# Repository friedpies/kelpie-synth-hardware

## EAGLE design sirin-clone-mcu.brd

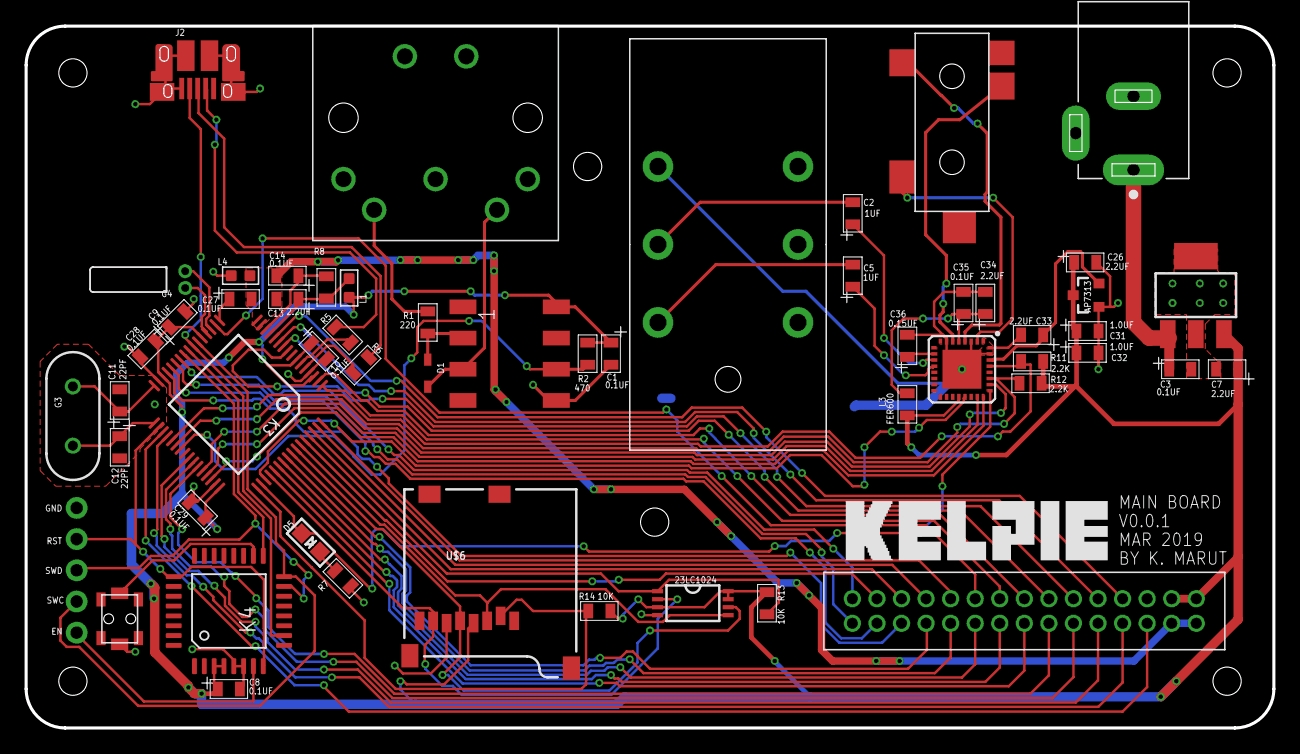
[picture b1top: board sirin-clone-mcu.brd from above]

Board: 2 copper layers, 101.6 x 57.1 mm, 55 parts (0 on the bottom side), 74 nets.

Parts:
C1, C3, C8, C9, C10, C14, C27, C28, C29, C35: 0.1UF; C_0805
C2, C5: 1UF; C_0805
C7, C13, C26, C33, C34: 2.2UF; C_0805
C11, C12: 22PF; C_0805
C31, C32: 1.0UF; C_0805
C36: 0.15UF; C_0805
D1: 1N4148WX-TP; SOD323
D5: ORANGE; CHIPLED_0805
D6: AP7313; SOT23-3
G3: 16MHz; HC49US
G4: 32.768kHz; TC26H
J1: PJ-002A; CUI_PJ-002A
J2: USB-MICROB-PTH-MILL
J3: 30_PIN_CONNECTOR_MALE; MOLEX_30PINCONNECTOR_2MM
J5: SWITCHCRAFT_PHONEJACK; STEREO_JACK_2SWITCH
J6: SWD_CONNECTOR; 1X5HEADER
K3: LQFP64-05
K4: LQFP32-08
L1, L4: L0603
L3: FER600; 0805
OK1: 6N138; DIP8
R1: 220; 0805
R2, R7, R8: 470; 0805
R5, R6: 33; 0805
R11, R12: 2.2K; 0805
R13, R14: 10K; 0805
S2: SWITCH_PTS820
T2: MCP1825S; SOT-223
U4: SGTL5000_32QFN; QFN-32-5MM
U5: 23LC1024; TSSOP8
U$1: MIDI_CONNECTOR; DIN_SDS_50J
U$3: STEREO_LINE_OUT_JACK; AMPHENOL_STEREO_JACK
U$6: MICROSD; MICRO-SD-SOCKET

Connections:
3.3V: C1.+, C7.+, C8.+, C9.+, C10.+, C26.+, C28.+, C29.+, C31.+, C32.+, D6.IN, J3.P$14, J3.P$15, K3.3, K3.7, K3.21, K3.30, K3.48, K4.3, K4.4, L1.2, L3.1, OK1.8, R2.2, R11.2, R12.2, R13.1, R14.2, T2.3, U4.20, U5.3, U5.7, U5.8, U$6.VCC(4)
AGND: C13.-, C14.-, C27.-, J3.P$29, J3.P$30, K3.15, K3.16, L4.2
AREF: C14.+, K3.14, R8.2
D+: J2.D+, R6.1
D-: J2.D-, R5.1
EN': J6.5, K4.7
GND: C1.-, C3.-, C7.-, C8.-, C9.-, C10.-, C11.-, C12.-, C26.-, C28.-, C29.-, C31.-, C32.-, C33.-, C34.-, C35.-, C36.-, D6.GND, J1.2, J2.GND, J2.SHIELD, J2.SHIELD2, J2.SHIELD3, J2.SHIELD4, J2.SHIELD5, J2.SHIELD6, J2.SHIELD7, J2.SHIELD8, J2.SHIELD9, J2.SHIELD10, J3.P$13, J6.1, K3.4, K3.31, K3.47, K4.5, K4.6, L4.1, OK1.5, R7.1, S2.2, T2.2, T2.PAD, U4.1, U4.3, U4.7, U4.31, U4.32, U4.PAD, U5.4, U$3.4, U$6.GND(6)
unnamed: D1.A, OK1.3, U$1.5
unnamed: R1.2, U$1.4
unnamed: D1.C, OK1.2, R1.1
unnamed: C5.+, U4.12
unnamed: C2.+, U4.11
unnamed: C2.-, U$3.5
unnamed: K3.24, K4.17
unnamed: D5.C, R7.2
unnamed: G4.1, K3.20
unnamed: G4.2, K3.19
unnamed: C12.+, G3.2, K3.33
unnamed: C11.+, G3.1, K3.32
unnamed: C13.+, K3.13, L1.1, R8.1
unnamed: C27.+, K3.17
unnamed: C5.-, U$3.6
unnamed: C36.+, U4.10
unnamed: C33.+, D6.OUT, U4.30
unnamed: C34.+, C35.+, L3.2, U4.5
PIN0/MIDIIN: K3.39, OK1.6, R2.1
PIN2/SW1: J3.P$19, K3.57
PIN3/SW2: J3.P$17, K3.28
PIN4/SW3: J3.P$18, K3.29
PIN5/SW4: J3.P$5, K3.64
PIN6/CS: K3.61, R13.2, U5.1
PIN7/CMD: K3.59, U5.5, U$6.DI(3)
PIN8/MIDILED: J3.P$2, K3.60
PIN9/BCLK: K3.46, U4.24
PIN10/DAT3: K3.49, R14.1, U$6.CS(2)
PIN11/MCLK: K3.51, U4.21
PIN12/DAT0: K3.52, U5.2, U$6.DO(7)
PIN13/RX: D5.A, K3.50, U4.25
PIN14/CLK: K3.58, U5.6, U$6.SCLK(5)
PIN15/KNOB1(VOL): J3.P$24, K3.43
PIN16/KNOB2: J3.P$28, K3.35
PIN17/KNOB3: J3.P$27, K3.36
PIN18/SDA: K3.38, R12.1, U4.27
PIN19/SCL: K3.37, R11.1, U4.29
PIN20/KNOB4: J3.P$3, K3.62
PIN21/KNOB5: J3.P$4, K3.63
PIN22/TX: K3.44, U4.26
PIN23/LRCLK: K3.45, U4.23
PIN24/LED1: J3.P$16, K3.27
PIN25/LED2: J3.P$25, K3.42
PIN26/KNOB6: J3.P$8, K3.2
PIN27/KNOB7: J3.P$22, K3.54
PIN28/KNOB8: J3.P$23, K3.53
PIN29/KNOB9: J3.P$21, K3.55
PIN30/KNOB10: J3.P$20, K3.56
PIN31/KNOB11: J3.P$7, K3.1
PIN32/LED3: J3.P$26, K3.41
PIN33/LED4: J3.P$1, K3.26
PINA10/KNOB12: J3.P$10, K3.9
PINA11/KNOB13: J3.P$9, K3.10
PINA12/KNOB14: J3.P$11, K3.11
PINA13/KNOB15: J3.P$12, K3.12
PINA14/KNOB16: J3.P$6, K3.18
PROG: K4.18, S2.1
RING/R: J5.3, U4.2
RST: J6.2, K3.34, K4.8, K4.25
SLEEVE: J5.1, U4.4
SWC: J6.4, K3.22, K4.16
SWD: J6.3, K3.25, K4.15
TIP/L: J5.2, U4.6
USB_DM: K3.6, R5.2
USB_DP: K3.5, R6.2
USB_ID: J2.ID, K3.23, K4.10
VIN_5V: C3.+, J1.1, T2.1

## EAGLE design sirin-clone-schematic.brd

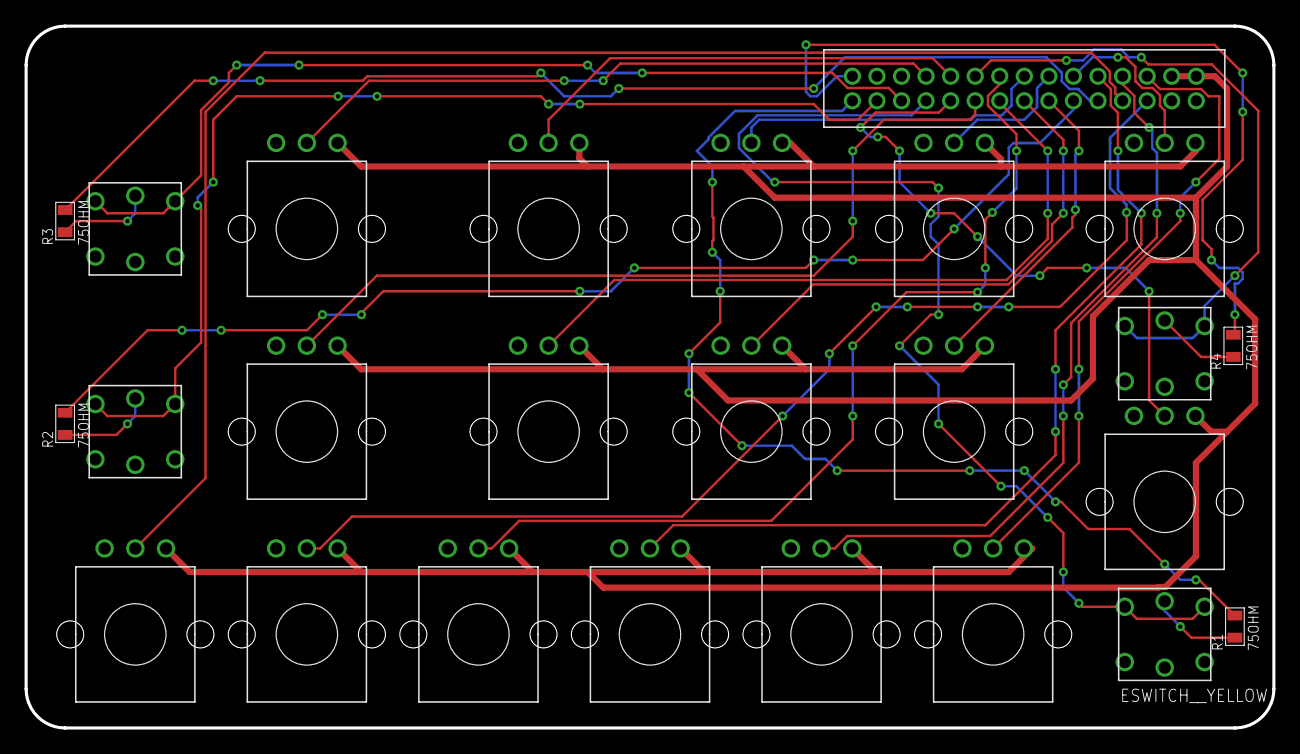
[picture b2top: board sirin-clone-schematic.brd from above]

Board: 2 copper layers, 101.6 x 57.1 mm, 25 parts (0 on the bottom side), 30 nets.

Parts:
J1: 30_PIN_CONNECTOR_MALE; MOLEX_30PINCONNECTOR_2MM
R1, R2, R3, R4: 75OHM; 0805
U$1, U$2, U$3, U$4, U$5, U$6, U$7, U$8, U$9, U$10, U$12, U$13, U$14, U$15, U$16, U$17: BOURNS_20K_POTENTIOMETER; BOURNS_PTV09
U$18, U$19, U$20, U$21: ESWITCH__YELLOW; ESWITCH_TL1240YQ1JCLR

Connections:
3.3V: J1.P$14, J1.P$15, U$1.1, U$2.1, U$3.1, U$4.1, U$5.1, U$6.1, U$7.1, U$8.1, U$9.1, U$10.1, U$12.1, U$13.1, U$14.1, U$15.1, U$16.1, U$17.1
GND: J1.P$29, J1.P$30, U$1.3, U$2.3, U$3.3, U$4.3, U$5.3, U$6.3, U$7.3, U$8.3, U$9.3, U$10.3, U$12.3, U$13.3, U$14.3, U$15.3, U$16.3, U$17.3, U$18.1, U$18.2, U$18.-, U$19.1, U$19.2, U$19.-, U$20.1, U$20.2, U$20.-, U$21.1, U$21.2, U$21.-
unnamed: R1.1, U$18.+
unnamed: R2.1, U$19.+
unnamed: R3.1, U$20.+
unnamed: R4.1, U$21.+
PIN2/SW1: J1.P$19, U$18.3, U$18.4
PIN3/SW2: J1.P$17, U$19.3, U$19.4
PIN4/SW3: J1.P$18, U$20.3, U$20.4
PIN5/SW4: J1.P$6, U$21.3, U$21.4
PIN15/KNOB1(VOL): J1.P$24, U$13.2
PIN16/KNOB2: J1.P$28, U$6.2
PIN17/KNOB3: J1.P$27, U$7.2
PIN20/KNOB4: J1.P$4, U$8.2
PIN21/KNOB5: J1.P$5, U$9.2
PIN24/LED1: J1.P$16, R1.2
PIN25/LED2: J1.P$25, R2.2
PIN26/KNOB6: J1.P$9, U$10.2
PIN27/KNOB7: J1.P$22, U$17.2
PIN28/KNOB8: J1.P$23, U$12.2
PIN29/KNOB9: J1.P$21, U$14.2
PIN30/KNOB10: J1.P$20, U$15.2
PIN31/KNOB11: J1.P$8, U$1.2
PIN32/LED3: J1.P$26, R3.2
PIN33/LED4: J1.P$1, R4.2
PINA10/KNOB12: J1.P$11, U$2.2
PINA11/KNOB13: J1.P$10, U$3.2
PINA12/KNOB14: J1.P$12, U$4.2
PINA13/KNOB15: J1.P$13, U$5.2
PINA14/KNOB16: J1.P$7, U$16.2

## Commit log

2019-03-03 fix folder structure and push
2019-03-13 work on lower pcb
2019-03-15 add midi
2019-03-16 work on connector options
2019-03-18 routing
2019-03-19 more routing
2019-03-20 lots o' routing
2019-03-21 ready for gerbers
2019-03-26 adding bom attributes
2019-03-26 placed bom order
